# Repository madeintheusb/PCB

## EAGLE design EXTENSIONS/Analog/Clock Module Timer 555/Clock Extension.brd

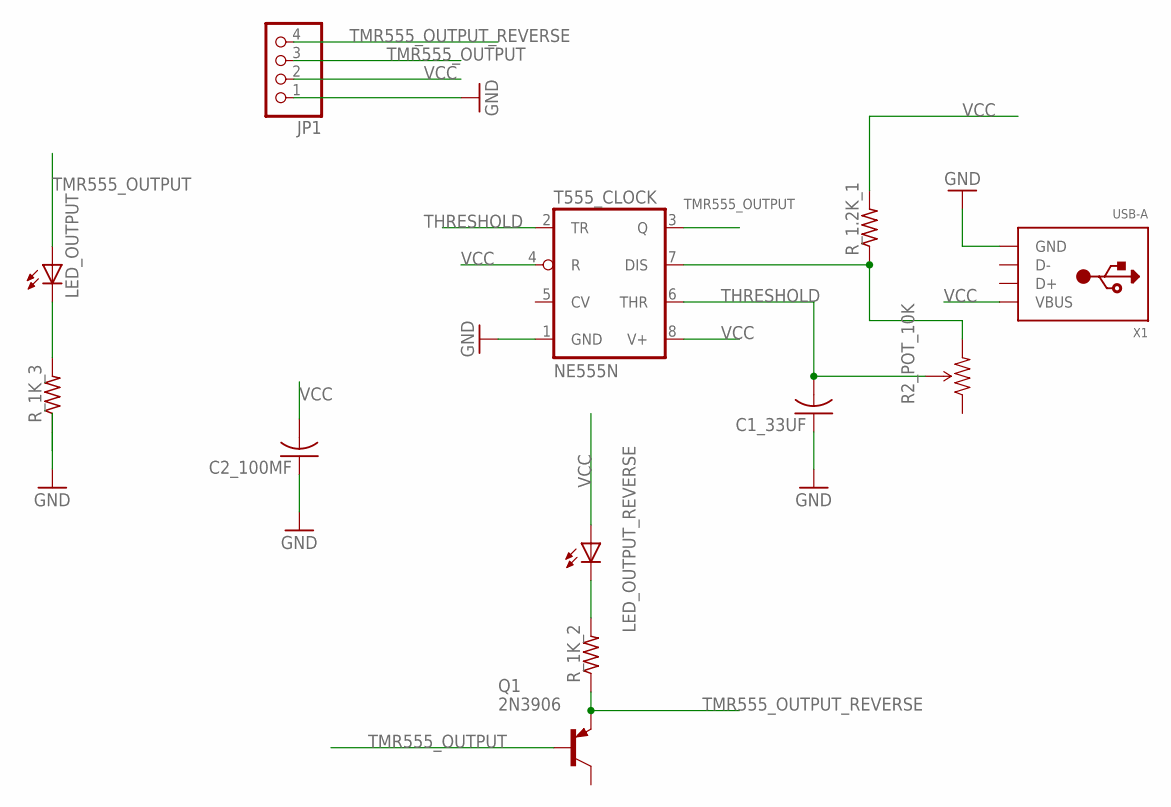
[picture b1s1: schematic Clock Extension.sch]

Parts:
C1_33UF, C2_100MF: C-US025-030X050; C025-030X050
JP1: PINHD-1X4; 1X04
LED_OUTPUT: LEDSMT1206; 1206
LED_OUTPUT_REVERSE: LEDSMT1206; 1206
Q1: 2N3906; TO92
R2_POT_10K: TRIMPOTPTH; TRIM_POT_PTH
R_1.2K_1, R_1K_2, R_1K_3: R-US_R1206; R1206
T555_CLOCK: NE555N; DIL08
X1: USB-A; MOLEX_480371000

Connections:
GND: C1_33UF.1, C2_100MF.1, JP1.1, R_1K_3.1, T555_CLOCK.1 (GND), X1.4 (GND)
unnamed: R2_POT_10K.3 (CW), R_1.2K_1.1, T555_CLOCK.7 (DIS)
unnamed: LED_OUTPUT.C, R_1K_3.2
unnamed: LED_OUTPUT_REVERSE.C, R_1K_2.2
THRESHOLD: C1_33UF.2, R2_POT_10K.2 (WIPER), T555_CLOCK.2 (TR), T555_CLOCK.6 (THR)
TMR555_OUTPUT: JP1.3, LED_OUTPUT.A, Q1.2 (B), T555_CLOCK.3 (Q)
TMR555_OUTPUT_REVERSE: JP1.4, Q1.3 (E), R_1K_2.1
VCC: C2_100MF.2, JP1.2, LED_OUTPUT_REVERSE.A, R_1.2K_1.2, T555_CLOCK.4 (R), T555_CLOCK.8 (V+), X1.1 (VBUS)

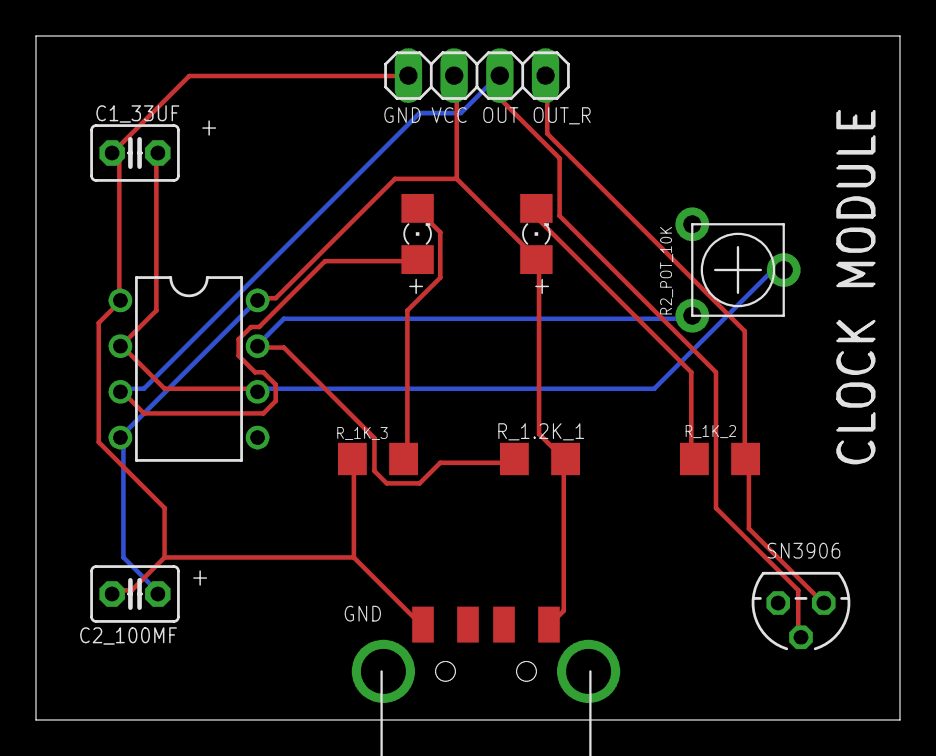
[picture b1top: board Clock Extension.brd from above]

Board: 2 copper layers, 48.0 x 38.0 mm, 12 parts (0 on the bottom side), 8 nets.

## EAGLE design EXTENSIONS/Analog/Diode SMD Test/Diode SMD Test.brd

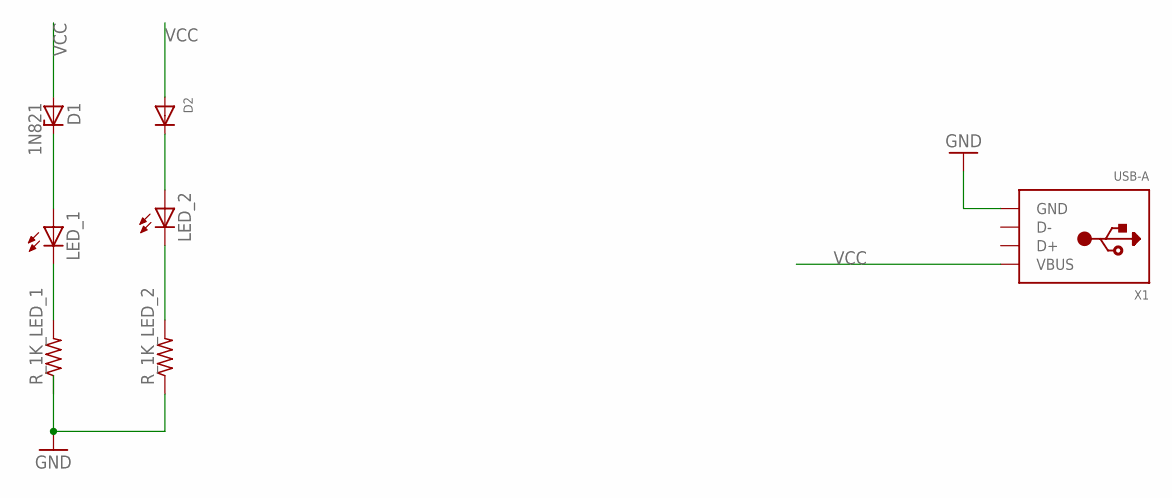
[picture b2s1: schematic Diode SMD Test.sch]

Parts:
D1: 1N821; DO35Z10
D2: DIODESMA; SMADIODE
LED_1, LED_2: LEDSMT1206; 1206
R_1K_LED_1, R_1K_LED_2: R-US_R1206; R1206
X1: USB-A; MOLEX_480371000

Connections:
GND: R_1K_LED_1.1, R_1K_LED_2.1, X1.4 (GND)
LED_1: LED_1.C, R_1K_LED_1.2
unnamed: D1.C, LED_1.A
unnamed: LED_2.C, R_1K_LED_2.2
unnamed: D2.C, LED_2.A
VCC: D1.A, D2.A, X1.1 (VBUS)

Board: 2 copper layers, 7 parts (0 on the bottom side), 6 nets, no tracks yet.

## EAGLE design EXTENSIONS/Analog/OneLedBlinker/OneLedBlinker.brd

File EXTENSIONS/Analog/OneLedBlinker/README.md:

http://www.talkingelectronics.com/te_interactive_index.html

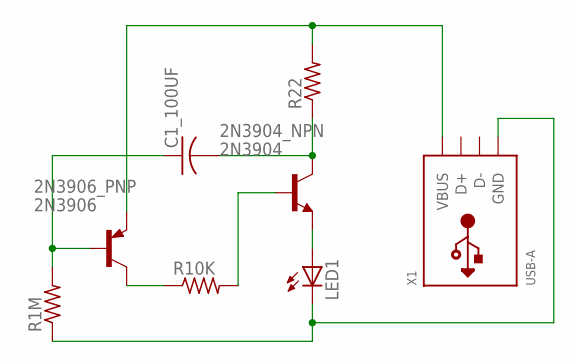
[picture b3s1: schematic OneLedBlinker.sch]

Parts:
2N3904_NPN: 2N3904; TO92
2N3906_PNP: 2N3906; TO92
C1_100UF: C-US025-030X050; C025-030X050
LED1: LED5MM
R1M, R10K, R22: R-US_0207/10; 0207/10
X1: USB-A; MOLEX_480371000

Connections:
unnamed: 2N3906_PNP.3 (E), R22.2, X1.1 (VBUS)
unnamed: 2N3904_NPN.1 (C), C1_100UF.2, R22.1
unnamed: 2N3904_NPN.3 (E), LED1.A
unnamed: LED1.K (C), R1M.1, X1.4 (GND)
unnamed: 2N3906_PNP.2 (B), C1_100UF.1, R1M.2
unnamed: 2N3906_PNP.1 (C), R10K.1
unnamed: 2N3904_NPN.2 (B), R10K.2

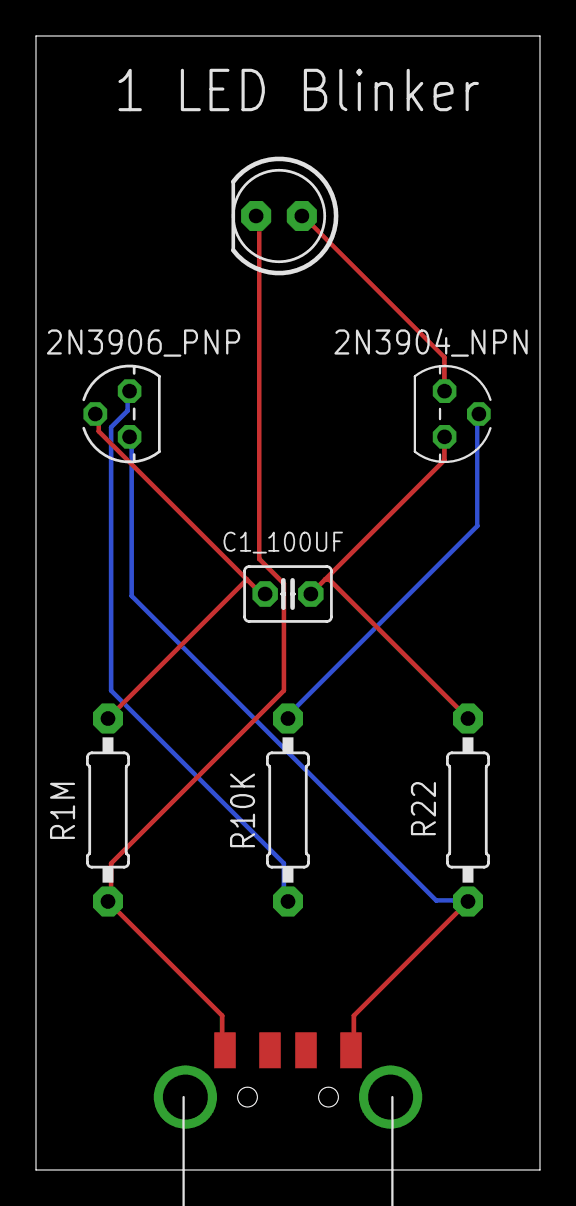
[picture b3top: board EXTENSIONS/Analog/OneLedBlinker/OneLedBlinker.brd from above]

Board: 2 copper layers, 28.0 x 63.0 mm, 8 parts (0 on the bottom side), 7 nets.

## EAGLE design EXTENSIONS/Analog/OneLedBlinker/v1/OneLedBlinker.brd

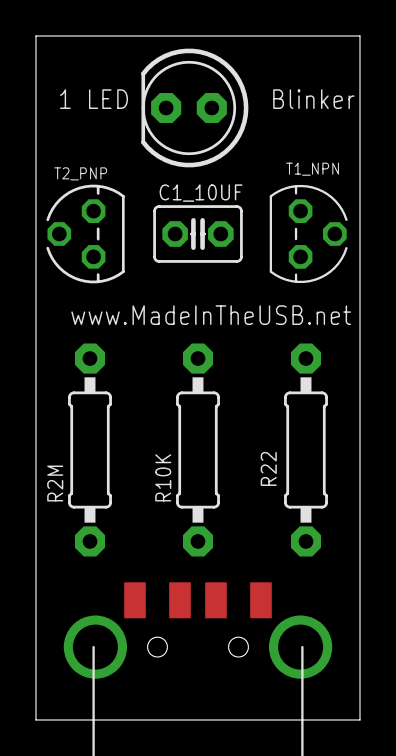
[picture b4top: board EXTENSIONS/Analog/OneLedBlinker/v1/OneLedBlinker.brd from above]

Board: 2 copper layers, 18.0 x 38.0 mm, 8 parts (0 on the bottom side), 7 nets, no tracks yet.

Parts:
C1_10UF: C025-030X050
LED1: LED5MM
R2M, R10K, R22: 0207/10
T1_NPN: 2N3904; TO92
T2_PNP: 2N3906; TO92
X1: USB-A; MOLEX_480371000

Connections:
unnamed: R22.2, T2_PNP.3, X1.1
unnamed: C1_10UF.2, R22.1, T1_NPN.1
unnamed: LED1.A, T1_NPN.3
unnamed: LED1.K, R2M.1, X1.4
unnamed: C1_10UF.1, R2M.2, T2_PNP.2
unnamed: R10K.1, T2_PNP.1
unnamed: R10K.2, T1_NPN.2

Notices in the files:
parts and their libraries:
SparkFun-Electromechanical: Licensing: Creative Commons ShareAlike 4.0 International - https://creativecommons.org/licenses/by-sa/4.0
